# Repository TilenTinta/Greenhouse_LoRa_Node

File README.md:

# Greenhouse LoRa Node

**Greenhouse LoRa Node** is an open-source monitoring system designed for use in greenhouses, orchards or other agricultural environments. This project includes all the necessary components to build the system, including:

- A custom PCB for the node (supports LoRa or SIM card communication),
- Firmware for the PCB,
- PCB casing,
- Server terminal application,
- GUI template using Grafana.

---

## PCB

The PCB is a two-layer board that integrates essential hardware components. It is versatile and supports different communication modules. Users can choose between a LoRa module or a SIM card module (both cannot be used simultaneously). 

### Features
- LDO voltage regulator - 3.3V for mcu and sensors.
- Direct battery power if STM32L151 is used,
- Step-up converter - 4V for SIM module only,
- Battery voltage monitoring,
- Battery cell holder for 18650 cells,
- Three connectors:
  - Earth humidity probe
  - AUX1 (I2C interface)
  - AUX2 (SPI interface),
- Support for LoRa module (RFM95W / SX1276) or SIM module (SIM800L),
- u.FL antenna connector,
- BME280 sensor (measures air temperature, humidity, and pressure),
- MCU: STM32F103C8T6 or STM32L151C8T6,
- 10-pin JTAG programming connector.

---

## Firmware

The firmware is written entirely in C using STM CubeIDE. It is designed to be easily updated or modified. The MCU supports multiple sleep modes for power optimization, which can be configured directly in the code.

The project does not include the `keys.h` file, as it contains user-specific information. The structure of the `keys.h` file is as follows:

```c
#ifndef KEYS_H_
#define KEYS_H_

#define DEVICE_ID            1       // ID number of the node

#define DEVICE_ADDRESS       {0x01, 0x23, 0x45, 0x56}
#define APPSKEY              {0x01, 0x23, 0x45, 0x67, 0x89, 0x10, 0x11, 0x12, 0x13, 0x14, 0x15, 0x16, 0x17, 0x18, 0x19, 0x20}
#define NWKSKEY              {0x01, 0x23, 0x45, 0x67, 0x89, 0x10, 0x11, 0x12, 0x13, 0x14, 0x15, 0x16, 0x17, 0x18, 0x19, 0x20}

#endif
```

The library for the RFM95W LoRa module is based on the repository linked below, with slight modifications made for this project: [https://github.com/henriheimann/stm32-hal-rfm95](https://github.com/henriheimann/stm32-hal-rfm95)

> [!CAUTION]
> When using the **RFM95W LoRa module** and the graphical peripheral editor in **CubeIDE**, additional code modifications are required. After saving changes in the IDE, the auto-generated code will be overwritten, re-enabling all IRQs by default. 
> The **RFM95W module** generates a 1 MHz digital signal on one of its IRQ pins at boot. If interrupts are not properly initialized, this can trigger errors in the MCU. To prevent this issue, **all interrupts must be disabled until the module is fully initialized**.

This project includes two firmware versions for two different microcontrollers. The firmware in the `Firmware_F103` folder was written for the STM32F103xx microcontroller and represents the initial version of the firmware. Due to issues with power consumption, the microcontroller was replaced with an STM32L151xx. The firmware in the `Firmware_L151` folder is the latest version, incorporating all modifications made to the PCB.

### Current consumption:
The current firmware is optimized for the LoRa module and uses Standby sleep mode. In this configuration, the PCB draws ~60 µA while asleep. This isn’t ideal yet, but it’s sufficient for initial tests. Bench measurements suggest the remaining overhead lies between the MCU and the RFM95W.
At 60 µA, a 3500 mAh 18650 cell yields a theoretical battery life of ~6 years, not accounting for self-discharge, temperature...

---

## Case

The PCB case is 3D printed using PETG filament on a standard FDM 3D printer. When deploying the node outdoors, ensure the filament can withstand UV exposure. Materials like ASA or ABS might be more suitable for such environments.

### Design Features:
- The case has a dedicated section with perforations to allow airflow near the sensor, enabling accurate air parameter measurements while protecting the rest of the PCB from external conditions.
- A groove runs along the perimeter of the lower part of the case, designed to fit a 3D-printed seal made from flexible materials like TPU or TPE. This ensures a better seal to protect the internal components.

### Notes:
- The design is optimized for easy replication using commonly available 3D printing materials and techniques.
- Consider using higher-temperature and UV-resistant materials for long-term outdoor use.

---

## Server Application

The server application is entirely written in Python and is terminal-based. Every operation performed by the application is logged into a log file for future inspection in case of issues. 

### Features
- Connects to your LoRaWAN devices on TTN via MQTT.
- Configurable `ttn_config.json` for easy integration.
- Configurable `InfluxDB_config.json` for easy integration.
- Supports multiple devices under a single application.

### Configuration Files

Upon boot, the application requires two JSON files to load all the configurations for the database and MQTT connection to the TTN broker:

1. **`InfluxDB_config.json`**  
   Configuration file for connecting to the InfluxDB database:
   ```json
   {
       "_comment": "JSON config file for database connection",
       "url": "http://localhost:8086",
       "org": "tinta",
       "token": "XXXXXXXXXXXXXXXXXXXXXXXXXXXXXXXXXXXXXXXXXX",
       "bucket": "bucket_name",
       "timezone": "Europe/Ljubljana"
   }
    ```

2. **`ttn_config.json`** 
    ```json
    {
        "_comment": "JSON config file for mqttTTN connection",
        "app_id": "lora-home-node",
        "username": "lora-home-node@ttn",
        "access_key": "XXXXXXXXXXXXXXXXXXXXXXXXXXX.XXXXXXXXXXXXXXXXXXXXXXXXX",
        "mqtt_broker": "eu1.cloud.thethings.network",
        "mqtt_port": 1883,
        "topic": "v3/lora-home-node@ttn/devices/+/up" 
    }
    ```

### Prerequirements

Before running the application, ensure you have the required dependencies installed. The following packages are necessary:

``` bash
pip install json paho-mqtt psycopg2 influxdb-client pytz logging socket base64
```

---

## Database

This project utilizes **InfluxDB** as its primary database solution. InfluxDB was selected due to its high efficiency in handling time-series data and its seamless integration with **Grafana**, which simplifies data visualization and analysis. By leveraging InfluxDB's ability to store data in a **time-series format**, this project ensures scalability for managing and analyzing temporal data.

### Notes:
- Ensure that InfluxDB is properly configured to handle the expected volume of data from the monitoring nodes.

---

## Grafana

This repository contains pre-configured Grafana UI files designed to read and present data from sensors in an intuitive and visually appealing way. These files provide a basic setup to help you quickly get started with monitoring and analyzing your sensor data using Grafana's powerful dashboard capabilities.

### Requirements:
- **Grafana** and **InfluxDB** should be installed on either a Raspberry Pi or a home server (depending on your setup).
- Ensure the terminal application is run on the same machine where the database and Grafana are installed.

---

## Docker Setup

This repository includes Docker support for easier and faster deployment on the server-side. The Docker setup contains:
- **InfluxDB** (Database)
- **Grafana** (Visualization Tool)
- **Python Server Application** (`server_app`)

> [!CAUTION]
Before running the Docker setup, the `docker-compose.yml` file must be modified to suit your specific preferences, such as:
- Network configurations,
- Volume mappings,
- Environment variables for InfluxDB, Grafana, and the Python application,
- Ports for external access,
- etc.

### Building the Container

To build the Docker containers, first navigate to the `Docker` folder in your terminal:

``` bash
cd /path/to/Docker
```
then run:
``` bash
docker-compose build
```
Once the container is build start it and set it up as you want.
``` bash
docker-compose up -d
```

### Acces containers
After running the containers, you can access:
- Grafana: http://localhost:3000 (default credentials: admin / admin123)
- InfluxDB: http://localhost:8086 (default credentials: admin / admin123)

Make sure your Grafana instance is properly configured to read from InfluxDB.

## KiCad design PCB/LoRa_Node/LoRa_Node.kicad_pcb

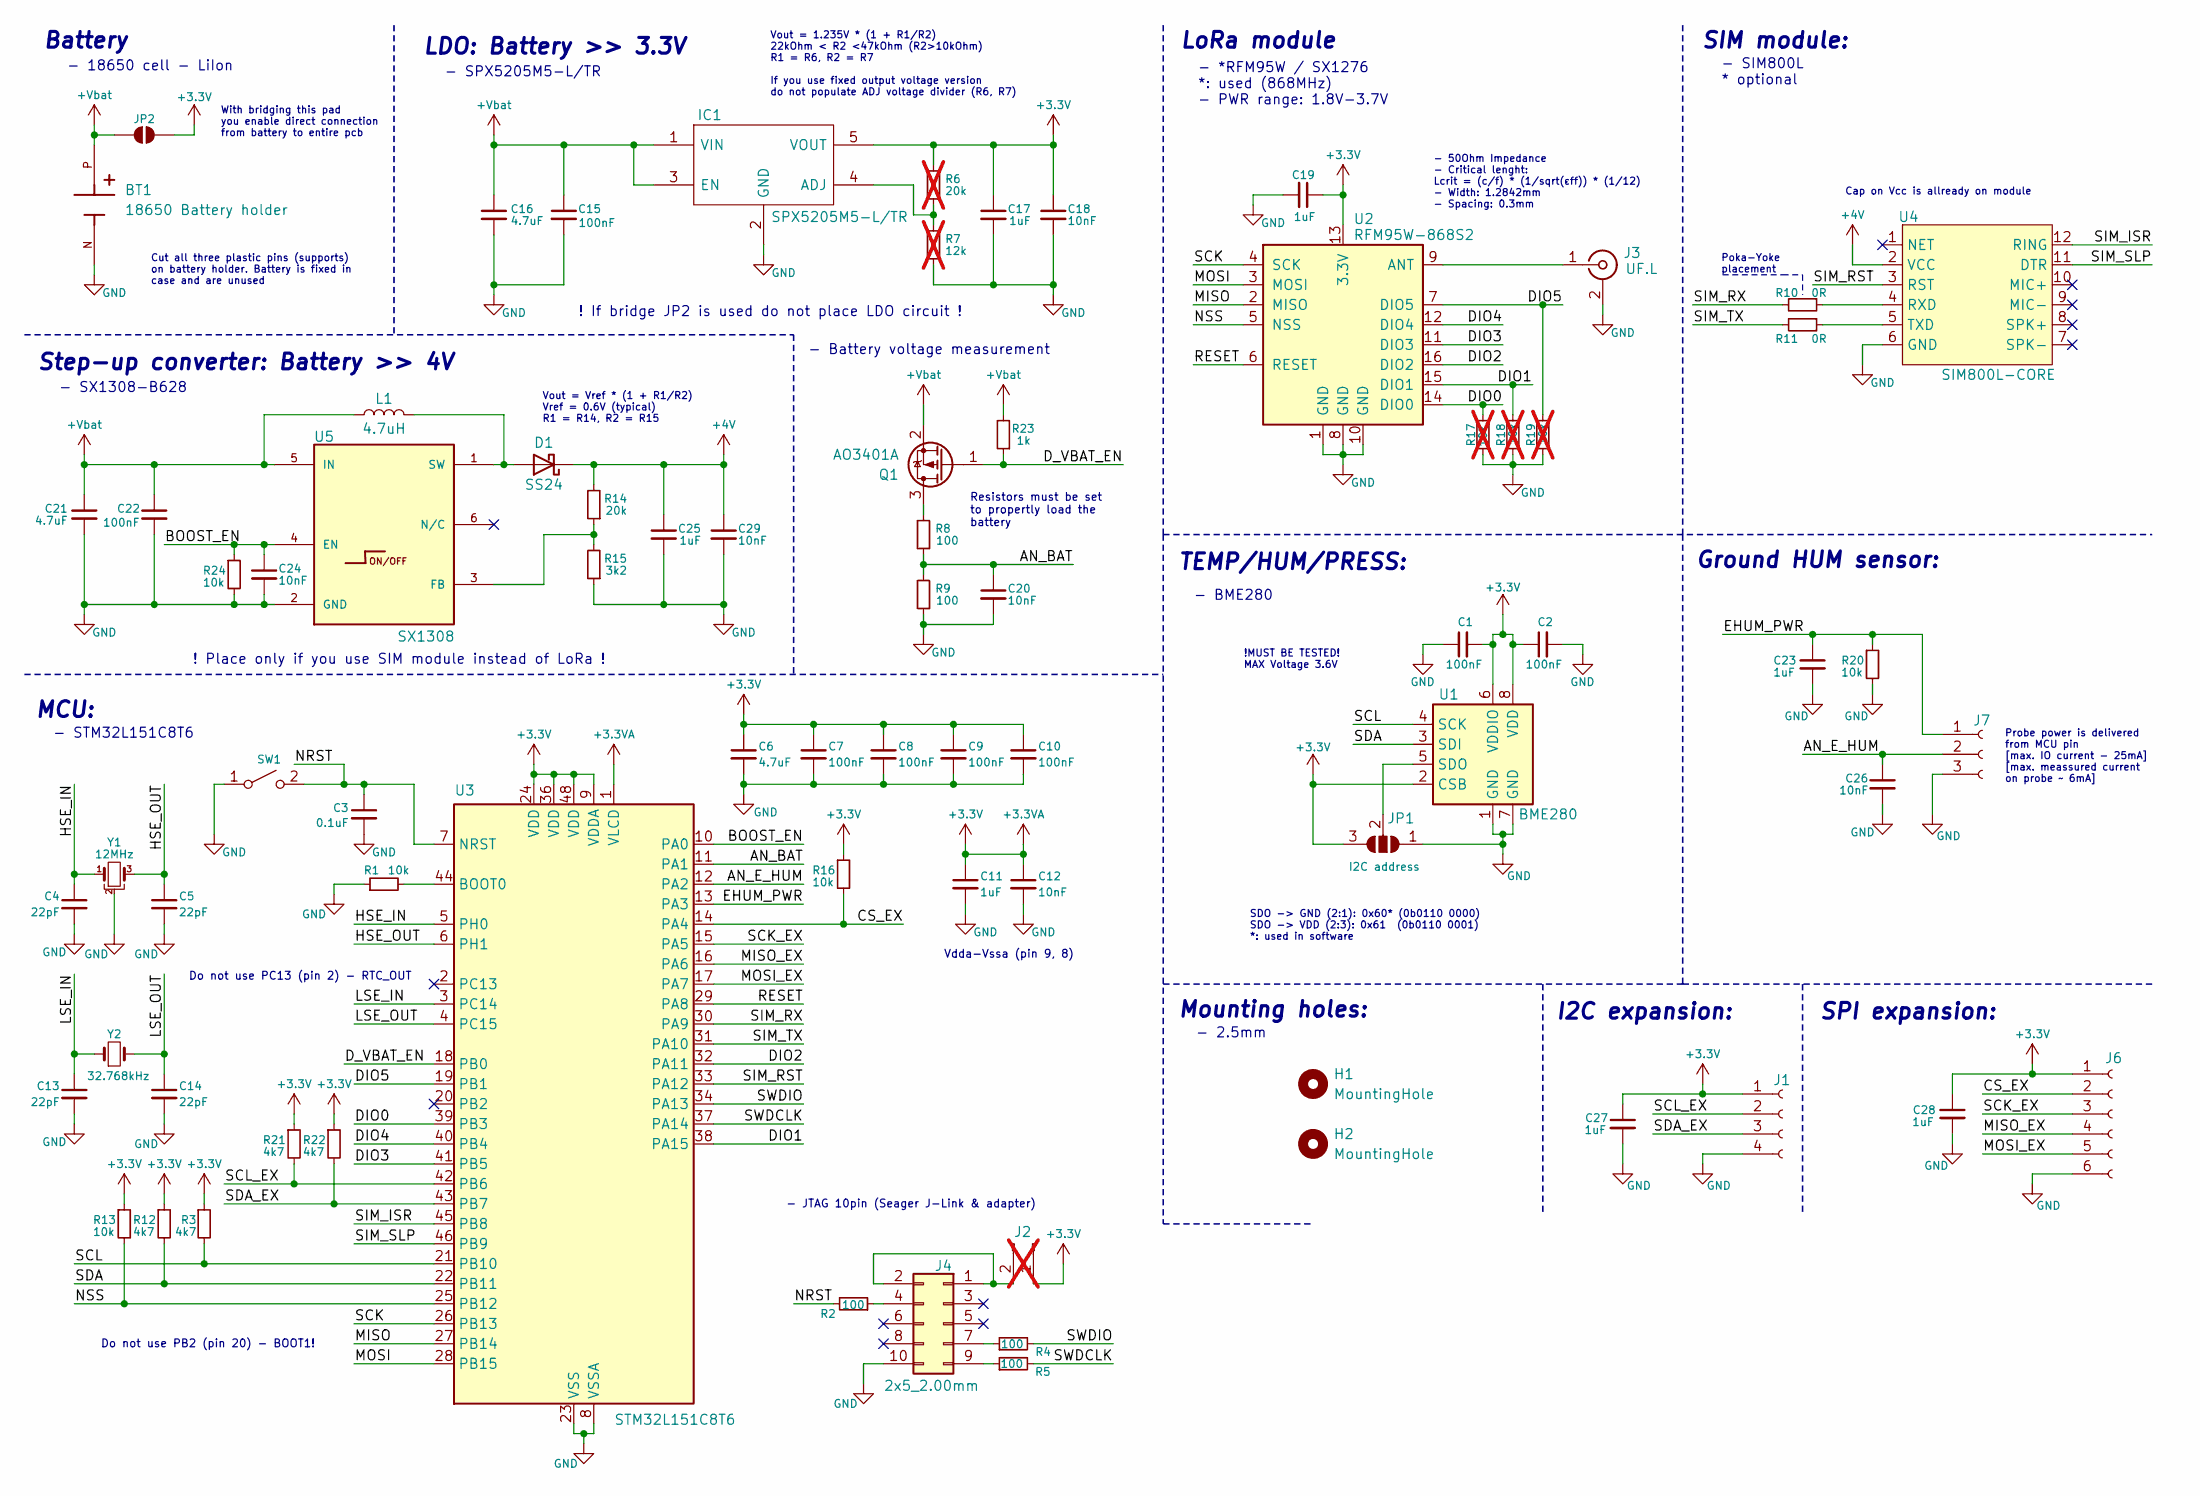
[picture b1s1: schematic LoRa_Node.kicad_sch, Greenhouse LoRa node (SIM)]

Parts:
BT1: 18650 Battery holder; PARTREV E
C1, C2, C15, C22: 100nF; C_0603_1608Metric
C3: 0.1uF; C_0603_1608Metric
C4, C5, C13, C14: 22pF; C_0402_1005Metric
C6: 4.7uF; C_0402_1005Metric
C7, C8, C9, C10: 100nF; C_0402_1005Metric
C11: 1uF; C_0402_1005Metric
C12: 10nF; C_0402_1005Metric
C16, C21: 4.7uF; C_1206_3216Metric
C17, C19, C23, C25, C27, C28: 1uF; C_0603_1608Metric
C18, C20, C24, C26, C29: 10nF; C_0603_1608Metric
D1: SS24; D_SMA
H1, H2: MountingHole; MountingHole_3.2mm_M3
IC1: SPX5205M5-L/TR; SOT95P280X145-5N; Manufacturer_Part_Number SPX5205M5-L-3-3/TR; Mouser Part Number 701-SPX5205M5-L-33TR
J1: Conn_01x04_Socket; Hirose_DF13-04P-1.25DSA_1x04_P1.25mm_Vertical
J2: Conn_01x02_Pin; PinHeader_1x02_P2.54mm_Vertical; not fitted
J3: UF.L; U.FL_Molex_MCRF_73412-0110_Vertical
J4: 2x5_2.00mm; PinHeader_2x05_P2.00mm_Vertical_SMD
J6: Conn_01x06_Socket; Hirose_DF13-06P-1.25DSA_1x06_P1.25mm_Vertical
J7: Conn_01x03_Socket; Hirose_DF13-03P-1.25DSA_1x03_P1.25mm_Vertical
JP1: I2C address; SolderJumper-3_P1.3mm_Open_RoundedPad1.0x1.5mm_NumberLabels
JP2: SolderJumper_2_Open; SolderJumper-2_P1.3mm_Open_RoundedPad1.0x1.5mm
L1: 4.7uH; L_Cenker_CKCS4020
Q1: AO3401A; SOT-23
R1, R13, R16, R20, R24: 10k; R_0603_1608Metric
R2, R4, R5, R8, R9: 100; R_0603_1608Metric
R3, R12, R21, R22: 4k7; R_0603_1608Metric
R6: 20k; R_0603_1608Metric; not fitted
R7: 12k; R_0603_1608Metric; not fitted
R10, R11: 0R; R_0603_1608Metric
R14: 20k; R_0603_1608Metric
R15: 3k2; R_0603_1608Metric
R17, R18, R19: 10k; R_0603_1608Metric; not fitted
R23: 1k; R_0603_1608Metric
SW1: SW_SPST; SW_Push_1P1T_NO_CK_KMR2
U1: BME280; Bosch_LGA-8_2x2.5mm_P0.65mm_ClockwisePinNumbering
U2: RFM95W-868S2; HOPERF_RFM9XW_SMD
U3: STM32L151C8T6; LQFP-48_7x7mm_P0.5mm
U4: SIM800L-CORE
U5: SX1308; SOT-23-6
Y1: 12MHz; Resonator_SMD_Murata_CSTxExxV-3Pin_3.0x1.1mm
Y2: 32.768kHz; Crystal_SMD_3215-2Pin_3.2x1.5mm

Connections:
+3.3V: C1.2, C2.1, C6.1, C7.1, C8.1, C9.1, C10.1, C11.1, C12.1, C17.1, C18.1, C19.1, C27.1, C28.1, IC1.5 (VOUT), J1.1, J2.1, J6.1, JP1.3 (B), JP2.2 (B), R3.1, R6.2, R12.1, R13.1, R16.1, R21.1, R22.1, U1.2 (CSB), U1.6 (VDDIO), U1.8 (VDD), U2.13 (3.3V), U3.1 (VLCD), U3.9 (VDDA), U3.24 (VDD), U3.36 (VDD), U3.48 (VDD)
+4V: C25.1, C29.1, D1.1 (K), R14.2, U4.2 (VCC)
+Vbat: BT1.P, C15.1, C16.1, C21.1, C22.1, IC1.1 (VIN), IC1.3 (EN), JP2.1 (A), L1.1, Q1.2 (S), R23.2, U5.5 (IN)
/AN_BAT: C20.1, R8.1, R9.2, U3.11 (PA1)
/AN_E_HUM: C26.1, J7.2, U3.12 (PA2)
/BOOST_EN: C24.1, R24.1, U3.10 (PA0), U5.4 (EN)
/CS_EX: J6.2, R16.2, U3.14 (PA4)
/DIO0: R17.2, U2.14 (DIO0), U3.39 (PB3)
/DIO1: R18.2, U2.15 (DIO1), U3.38 (PA15)
/DIO2: U2.16 (DIO2), U3.32 (PA11)
/DIO3: U2.11 (DIO3), U3.41 (PB5)
/DIO4: U2.12 (DIO4), U3.40 (PB4)
/DIO5: R19.2, U2.7 (DIO5), U3.19 (PB1)
/D_VBAT_EN: Q1.1 (G), R23.1, U3.18 (PB0)
/EHUM_PWR: C23.1, J7.1, R20.1, U3.13 (PA3)
/HSE_IN: C4.1, U3.5 (PH0), Y1.1
/HSE_OUT: C5.1, U3.6 (PH1), Y1.3
/LSE_IN: C13.1, U3.3 (PC14), Y2.1
/LSE_OUT: C14.1, U3.4 (PC15), Y2.2
/MISO: U2.2 (MISO), U3.27 (PB14)
/MISO_EX: J6.4, U3.16 (PA6)
/MOSI: U2.3 (MOSI), U3.28 (PB15)
/MOSI_EX: J6.5, U3.17 (PA7)
/NRST: C3.1, R2.2, SW1.2 (B), U3.7 (NRST)
/NSS: R13.2, U2.5 (NSS), U3.25 (PB12)
/RESET: U2.6 (RESET), U3.29 (PA8)
/SCK: U2.4 (SCK), U3.26 (PB13)
/SCK_EX: J6.3, U3.15 (PA5)
/SCL: R3.2, U1.4 (SCK), U3.21 (PB10)
/SCL_EX: J1.2, R21.2, U3.42 (PB6)
/SDA: R12.2, U1.3 (SDI), U3.22 (PB11)
/SDA_EX: J1.3, R22.2, U3.43 (PB7)
/SIM_ISR: U3.45 (PB8), U4.12 (RING)
/SIM_RST: U3.33 (PA12), U4.3 (RST)
/SIM_RX: R10.2, U3.30 (PA9)
/SIM_SLP: U3.46 (PB9), U4.11 (DTR)
/SIM_TX: R11.2, U3.31 (PA10)
/SWDCLK: R5.2, U3.37 (PA14)
/SWDIO: R4.2, U3.34 (PA13)
GND: BT1.N, C1.1, C2.2, C3.2, C4.2, C5.2, C6.2, C7.2, C8.2, C9.2, C10.2, C11.2, C12.2, C13.2, C14.2, C15.2, C16.2, C17.2, C18.2, C19.2, C20.2, C21.2, C22.2, C23.2, C24.2, C25.2, C26.2, C27.2, C28.2, C29.2, IC1.2 (GND), J1.4, J3.2 (Ext), J4.10, J6.6, J7.3, JP1.1 (A), R1.1, R7.1, R9.1, R15.1, R17.1, R18.1, R19.1, R20.2, R24.2, SW1.1 (A), U1.1 (GND), U1.7 (GND), U2.1 (GND), U2.8 (GND), U2.10 (GND), U3.8 (VSSA), U3.23 (VSS), U3.35 (VSS), U3.47 (VSS), U4.6 (GND), U5.2 (GND), Y1.2
unnamed: D1.2 (A), L1.2, U5.1 (SW)
unnamed: IC1.4 (ADJ), R6.1, R7.2
unnamed: J2.2, J4.1, J4.2
unnamed: J3.1 (In), U2.9 (ANT)
unnamed: J4.4, R2.1
unnamed: J4.7, R4.1
unnamed: J4.9, R5.1
unnamed: JP1.2 (C), U1.5 (SDO)
unnamed: Q1.3 (D), R8.2
unnamed: R1.2, U3.44 (BOOT0)
unnamed: R10.1, U4.4 (RXD)
unnamed: R11.1, U4.5 (TXD)
unnamed: R14.1, R15.2, U5.3 (FB)

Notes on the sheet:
LDO: Battery >> 3.3V
- SX1308-B628
Probe power is delivered from MCU pin [max. IO current - 25mA] [max. meassured current on probe ~ 6mA]
- BME280
LoRa module
!MUST BE TESTED! MAX Voltage 3.6V
With bridging this pad you enable direct connection from battery to entire pcb
Mounting holes:
Cut all three plastic pins (supports) on battery holder. Battery is fixed in case and are unused
- Battery voltage measurement
Vout = 1.235V * (1 + R1/R2) 22kOhm < R2 <47kOhm (R2>10kOhm) R1 = R6, R2 = R7 If you use fixed output voltage version do not populate ADJ voltage divider (R6, R7)
SPI expansion:
- SIM800L * optional
Do not use PC13 (pin 2) - RTC_OUT
SDO -> GND (2:1): 0x60* (0b0110 0000) SDO -> VDD (2:3): 0x61 (0b0110 0001) *: used in software
- SPX5205M5-L/TR
Vdda-Vssa (pin 9, 8)
Ground HUM sensor:
- 2.5mm
Battery
! If bridge JP2 is used do not place LDO circuit !
Poka-Yoke placement
MCU:
! Place only if you use SIM module instead of LoRa !
Cap on Vcc is allready on module
- 50Ohm Impedance - Critical lenght: Lcrit = (c/f) * (1/sqrt(εff)) * (1/12) - Width: 1.2842mm - Spacing: 0.3mm
Resistors must be set to propertly load the battery
Vout = Vref * (1 + R1/R2) Vref = 0.6V (typical) R1 = R14, R2 = R15
- 18650 cell - LiIon
Step-up converter: Battery >> 4V
TEMP/HUM/PRESS:
Do not use PB2 (pin 20) - BOOT1!
- STM32L151C8T6
I2C expansion:
- *RFM95W / SX1276 *: used (868MHz) - PWR range: 1.8V-3.7V
- JTAG 10pin (Seager J-Link & adapter)
SIM module:

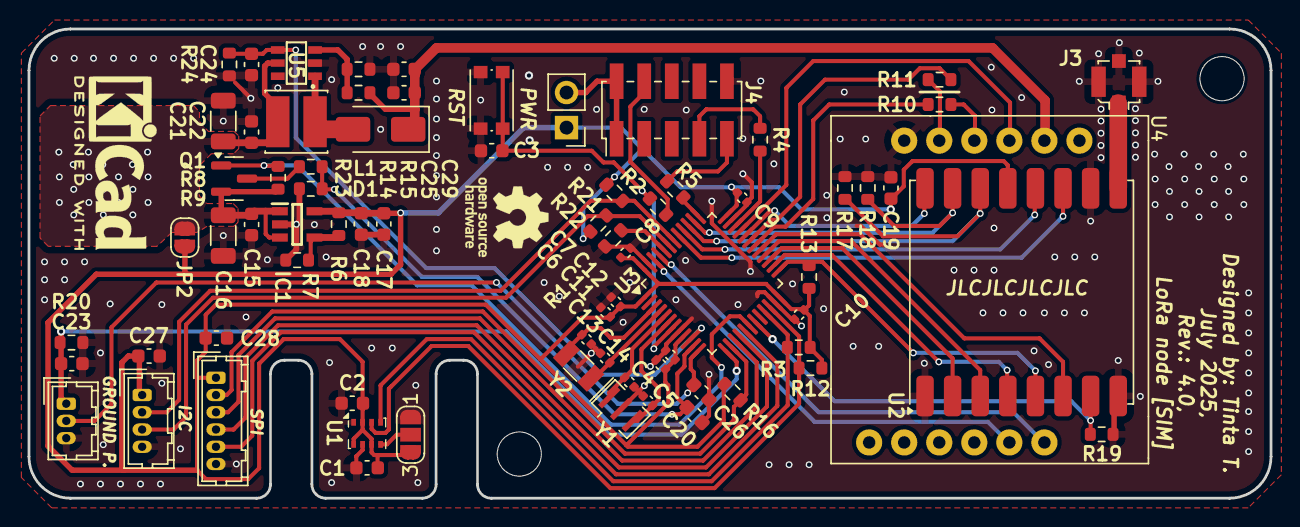
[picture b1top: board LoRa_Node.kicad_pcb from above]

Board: 2 copper layers, 90.0 x 34.0 mm, 76 parts (1 on the bottom side), 53 nets.

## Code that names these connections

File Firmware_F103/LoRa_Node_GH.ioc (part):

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Mcu.Name=STM32F103C(8-B)Tx
Mcu.Package=LQFP48
Mcu.UserName=STM32F103CBTx
PA0-WKUP.GPIOParameters=GPIO_Label
PA0-WKUP.GPIO_Label=BOOST_EN
PA0-WKUP.Signal=GPIO_Output
PA1.GPIOParameters=GPIO_Label
PA1.GPIO_Label=AN_BAT
PA1.Signal=ADCx_IN1
PA10.Mode=Asynchronous
PA10.Signal=USART1_RX
PA11.GPIOParameters=GPIO_Label
PA11.GPIO_Label=DIO2
PA11.Signal=GPIO_Input
PA12.GPIOParameters=GPIO_Label
PA12.GPIO_Label=SIM_RST
PA12.Signal=GPXTI12
PA13.Mode=Serial_Wire
PA13.Signal=SYS_JTMS-SWDIO
PA14.Mode=Serial_Wire
PA14.Signal=SYS_JTCK-SWCLK
PA15.GPIOParameters=GPIO_PuPd,GPIO_Label
PA15.GPIO_Label=DIO1
PA15.GPIO_PuPd=GPIO_NOPULL
PA15.Signal=GPXTI15
PA2.GPIOParameters=GPIO_Label
PA2.GPIO_Label=AN_E_HUM
PA2.Signal=ADCx_IN2
PA3.GPIOParameters=GPIO_Label
PA3.GPIO_Label=EHUM_PWR
PA3.Signal=GPIO_Output
PA4.GPIOParameters=PinState,GPIO_Label
PA4.GPIO_Label=SPI_CS_EX
PA4.PinState=GPIO_PIN_SET
PA4.Signal=GPIO_Output
PA5.Mode=Full_Duplex_Master
PA5.Signal=SPI1_SCK
PA6.Mode=Full_Duplex_Master
PA6.Signal=SPI1_MISO
PA7.Mode=Full_Duplex_Master
PA7.Signal=SPI1_MOSI
PA8.GPIOParameters=GPIO_Speed,PinState,GPIO_PuPd,GPIO_Label
PA8.GPIO_Label=RESET
PA8.GPIO_PuPd=GPIO_PULLUP
PA8.GPIO_Speed=GPIO_SPEED_FREQ_LOW
PA8.PinState=GPIO_PIN_SET
PA8.Signal=GPIO_Output
PA9.Mode=Asynchronous
PA9.Signal=USART1_TX
PB0.GPIOParameters=GPIO_Label
PB0.GPIO_Label=D_VBAT_EN
PB0.Signal=GPIO_Output
PB1.GPIOParameters=GPIO_PuPd,GPIO_Label
PB1.GPIO_Label=DIO5
PB1.GPIO_PuPd=GPIO_NOPULL
PB1.Signal=GPXTI1
PB10.Mode=I2C
PB10.Signal=I2C2_SCL
PB11.Mode=I2C
PB11.Signal=I2C2_SDA
PB12.GPIOParameters=PinState,GPIO_PuPd,GPIO_Label
PB12.GPIO_Label=SPI2_NSS
PB12.GPIO_PuPd=GPIO_NOPULL
PB12.PinState=GPIO_PIN_SET
PB12.Signal=GPIO_Output
PB13.Mode=Full_Duplex_Master
PB13.Signal=SPI2_SCK
PB14.Mode=Full_Duplex_Master
PB14.Signal=SPI2_MISO
PB15.Mode=Full_Duplex_Master
PB15.Signal=SPI2_MOSI
PB2.GPIOParameters=GPIO_Label
PB2.GPIO_Label=UNUSED3
PB2.Signal=GPIO_Analog
PB3.GPIOParameters=GPIO_PuPd,GPIO_Label
PB3.GPIO_Label=DIO0
PB3.GPIO_PuPd=GPIO_NOPULL
PB3.Signal=GPXTI3
PB4.GPIOParameters=GPIO_Label
PB4.GPIO_Label=DIO4
PB4.Signal=GPIO_Input
PB5.GPIOParameters=GPIO_Label
PB5.GPIO_Label=DIO3
PB5.Signal=GPIO_Input
PB6.Mode=I2C
PB6.Signal=I2C1_SCL
PB7.Mode=I2C
PB7.Signal=I2C1_SDA
PB8.GPIOParameters=GPIO_Label
PB8.GPIO_Label=SIM_ISR
PB8.Signal=GPXTI8
PB9.GPIOParameters=GPIO_Label
PB9.GPIO_Label=SIM_SLP
PB9.Signal=GPIO_Output
PC13-TAMPER-RTC.Mode=RTC OUT
PC13-TAMPER-RTC.Signal=RTC_OUT
PC14-OSC32_IN.Mode=LSE-External-Oscillator
PC14-OSC32_IN.Signal=RCC_OSC32_IN
PC15-OSC32_OUT.Mode=LSE-External-Oscillator
PC15-OSC32_OUT.Signal=RCC_OSC32_OUT
PD0-OSC_IN.Mode=HSE-External-Oscillator
PD0-OSC_IN.Signal=RCC_OSC_IN
PD1-OSC_OUT.Mode=HSE-External-Oscillator
PD1-OSC_OUT.Signal=RCC_OSC_OUT
RCC.HSE_VALUE=12000000
RCC.SYSCLKFreq_VALUE=72000000
RCC.SYSCLKSource=RCC_SYSCLKSOURCE_PLLCLK
board=custom

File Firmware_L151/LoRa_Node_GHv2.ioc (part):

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Mcu.Name=STM32L151C(6-8-B)Tx
Mcu.Package=LQFP48
Mcu.UserName=STM32L151C8Tx
PA0-WKUP1.GPIOParameters=GPIO_PuPd,GPIO_Label
PA0-WKUP1.GPIO_Label=BOOST_EN
PA0-WKUP1.GPIO_PuPd=GPIO_NOPULL
PA0-WKUP1.Signal=GPIO_Output
PA1.GPIOParameters=GPIO_Label
PA1.GPIO_Label=AN_BAT
PA1.Mode=IN1
PA1.Signal=ADC_IN1
PA10.Signal=GPIO_Analog
PA11.GPIOParameters=GPIO_PuPd,GPIO_Label
PA11.GPIO_Label=DIO2
PA11.GPIO_PuPd=GPIO_NOPULL
PA11.Signal=GPIO_Input
PA12.Signal=GPIO_Analog
PA13.Mode=Serial_Wire
PA13.Signal=SYS_JTMS-SWDIO
PA14.Mode=Serial_Wire
PA14.Signal=SYS_JTCK-SWCLK
PA15.GPIOParameters=GPIO_PuPd,GPIO_Label
PA15.GPIO_Label=DIO1
PA15.GPIO_PuPd=GPIO_NOPULL
PA15.Signal=GPXTI15
PA2.GPIOParameters=GPIO_Label
PA2.GPIO_Label=AN_E_HUM
PA2.Mode=IN2
PA2.Signal=ADC_IN2
PA3.GPIOParameters=GPIO_Label
PA3.GPIO_Label=EHUM_PWR
PA3.Signal=GPIO_Output
PA4.GPIOParameters=PinState,GPIO_Label
PA4.GPIO_Label=SPI1_CS_EX
PA4.PinState=GPIO_PIN_SET
PA4.Signal=GPIO_Output
PA5.Mode=Full_Duplex_Master
PA5.Signal=SPI1_SCK
PA6.Mode=Full_Duplex_Master
PA6.Signal=SPI1_MISO
PA7.Mode=Full_Duplex_Master
PA7.Signal=SPI1_MOSI
PA8.GPIOParameters=GPIO_PuPd,GPIO_Label
PA8.GPIO_Label=RESET
PA8.GPIO_PuPd=GPIO_NOPULL
PA8.Signal=GPIO_Output
PA9.Signal=GPIO_Analog
PB0.GPIOParameters=PinState,GPIO_Label
PB0.GPIO_Label=D_VBAT_EN
PB0.PinState=GPIO_PIN_SET
PB0.Signal=GPIO_Output
PB1.GPIOParameters=GPIO_PuPd,GPIO_Label
PB1.GPIO_Label=DIO5
PB1.GPIO_PuPd=GPIO_NOPULL
PB1.Signal=GPXTI1
PB10.Mode=I2C
PB10.Signal=I2C2_SCL
PB11.Mode=I2C
PB11.Signal=I2C2_SDA
PB12.GPIOParameters=PinState,GPIO_Label
PB12.GPIO_Label=SPI2_NSS
PB12.PinState=GPIO_PIN_SET
PB12.Signal=GPIO_Output
PB13.Mode=Full_Duplex_Master
PB13.Signal=SPI2_SCK
PB14.Mode=Full_Duplex_Master
PB14.Signal=SPI2_MISO
PB15.Mode=Full_Duplex_Master
PB15.Signal=SPI2_MOSI
PB2.GPIOParameters=GPIO_Label
PB2.GPIO_Label=UNUSED1
PB2.Signal=GPIO_Analog
PB3.GPIOParameters=GPIO_PuPd,GPIO_Label
PB3.GPIO_Label=DIO0
PB3.GPIO_PuPd=GPIO_NOPULL
PB3.Signal=GPXTI3
PB4.GPIOParameters=GPIO_PuPd,GPIO_Label
PB4.GPIO_Label=DIO4
PB4.GPIO_PuPd=GPIO_NOPULL
PB4.Signal=GPIO_Input
PB5.GPIOParameters=GPIO_PuPd,GPIO_Label
PB5.GPIO_Label=DIO3
PB5.GPIO_PuPd=GPIO_NOPULL
PB5.Signal=GPIO_Input
PB6.Mode=I2C
PB6.Signal=I2C1_SCL
PB7.Mode=I2C
PB7.Signal=I2C1_SDA
PB8.Signal=GPIO_Analog
PB9.Signal=GPIO_Analog
PC14-OSC32_IN.Mode=LSE-External-Oscillator
PC14-OSC32_IN.Signal=RCC_OSC32_IN
PC15-OSC32_OUT.Mode=LSE-External-Oscillator
PC15-OSC32_OUT.Signal=RCC_OSC32_OUT
PH0-OSC_IN.Mode=HSE-External-Oscillator
PH0-OSC_IN.Signal=RCC_OSC_IN
PH1-OSC_OUT.Mode=HSE-External-Oscillator
PH1-OSC_OUT.Signal=RCC_OSC_OUT
RCC.HSE_VALUE=12000000
RCC.SYSCLKFreq_VALUE=32000000
RCC.SYSCLKSource=RCC_SYSCLKSOURCE_PLLCLK
board=custom

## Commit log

2024-11-24 Update: PCB, firmware, server app
2024-11-24 Update: server app
2024-12-16 Update
    PCB: added pull-downs on IRQ pins, SW: stable EXTI, reliable measurements
2024-12-24 First test version (finished)
2024-12-25 Update
    Humidity probe is rewired from the 3v3 to MCU pin for power
2024-12-28 README Update
2025-01-25 Update:
    4V bus update (step-up converter)
2025-01-26 Update: README - boost
2025-04-06 added Docker image for all the server applications
2025-05-31 PCB modifications, MCU replacement and FW migration
2025-06-19 ported SW to now MCU - untested
2025-08-02 update
    working code for new mcu, current consumption still 900uA
2025-08-02 update
    updated PCB
2025-09-07 Update
    firmware current optimisation
2025-09-07 Update
    PCB pdf
2025-09-24 Bugfix
    solved problem with LoRa packet counter (flash write error after sleep)
2025-09-25 Update
    code cleanup
2025-09-26 Update
    server app autostart
2025-09-27 Bugfix
    earth humidity and MBE280 power on delay
